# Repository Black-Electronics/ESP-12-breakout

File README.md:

# ESP-12 breakout board

---
## This is a work in progress
see [logs](https://hackaday.io/project/13018-esp-12e-breakout-board)

[Cern Open Hardware v1.2 Licence](http://www.ohwr.org/attachments/2388/cern_ohl_v_1_2.txt)

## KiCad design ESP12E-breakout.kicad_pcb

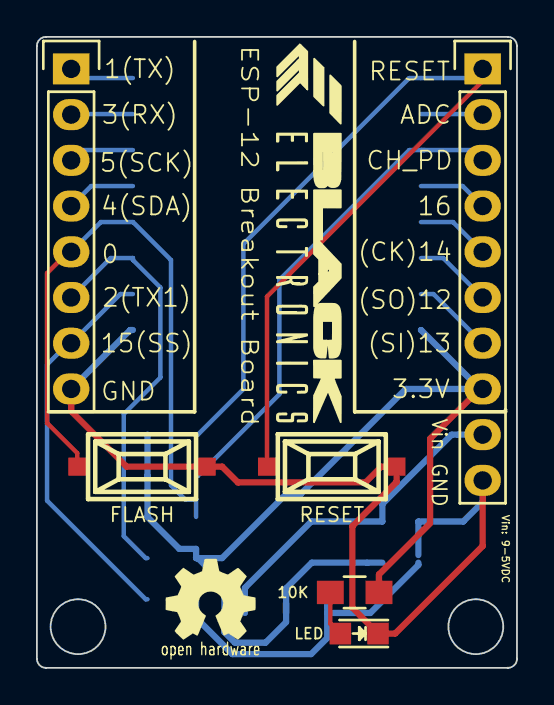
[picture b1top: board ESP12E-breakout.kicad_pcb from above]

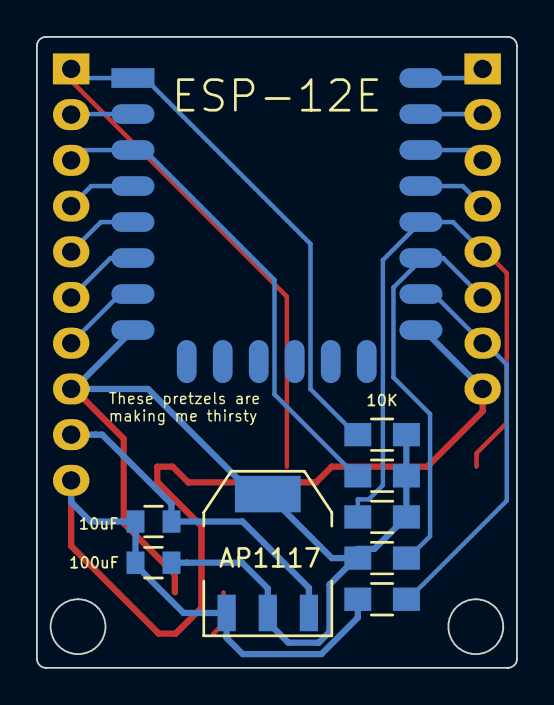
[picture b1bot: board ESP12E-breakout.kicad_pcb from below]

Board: 2 copper layers, 26.7 x 35.1 mm, 17 parts (9 on the bottom side), 18 nets.

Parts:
C1: 10uF; C_0805
C2: 100uF; C_0805
D1: LED; LED-0805
G0: LOGO; 3k5
G1: LOGO; oshw-logo-kicad-copper-10mm
P1: CONN_01X10; Pin_Header_Straight_1x10
P3: CONN_01X08; Pin_Header_Straight_1x08
R1, R2, R3, R4, R5, R6: 10K; R_0805_HandSoldering
SW1: RESET; smd_push
SW2: FLASH; smd_push
U1: ESP-12E
U2: AP1117; SOT-223_edit

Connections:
/0: P3.5, R3.1, SW2.1, U1.18
/2: P3.6, R4.1, U1.17
/3V3: C2.1, P1.8, R1.2, R2.2, R3.2, R4.2, R6.2, U1.8, U2.2
/4: P3.4, U1.19
/5: P3.3, U1.20
/5V: C1.1, P1.9, U2.3
/12: P1.6, U1.6
/13: P1.7, U1.7
/14: P1.5, U1.5
/15: P3.7, R5.2, U1.16
/16: P1.4, U1.4
/ADC: P1.2, U1.2
/CH_PD: P1.3, R2.1, U1.3
/RESET: P1.1, R1.1, SW1.2, U1.1
/RX: P3.2, U1.21
/TX: P3.1, U1.22
GND: C1.2, C2.2, D1.1, P1.10, P3.8, R5.1, SW1.1, SW2.2, U1.15, U2.1
unnamed: D1.2, R6.1

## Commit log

2016-08-07 Added license
2016-08-08 Added on board bi-directional 3v3-5V conversion
2016-08-08 added readme
2016-08-10 Keeping it simple Removed the level conversion, added regulator and other pull ups and pull donws.
2016-08-11 removed level converter, added regulator Keeping it simple.
2016-08-16 Ready for prototype run
2016-08-17 removed vias
2016-11-11 Sent for Fab
2016-11-12 3D renders
2016-11-12 Added renders to readme
